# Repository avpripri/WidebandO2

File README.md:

# WidebandO2

An Arduino sketch for controlling a Bosch LSU 4.9 Wideband Lambda sensor with minimal parts

The board used is the ProMicro (ATMEGA32U)
The project uses Visual Studio Code + PlatformIO but can easily be built in Arduino IDE by renaming main.cpp to main.ino.

## Update Jan-2021

Changes:
- PlatformIO
- ProMicro from Teensy 2.0 (just what I have handy)
- Redrafted the circuit for EasyEDA with gerbers, BOM & PnP for JLPCB orders 

## Required Libraries

* RunningAverage - http://playground.arduino.cc/Main/RunningAverage
* PIDLibrary - http://playground.arduino.cc/Code/PIDLibrary

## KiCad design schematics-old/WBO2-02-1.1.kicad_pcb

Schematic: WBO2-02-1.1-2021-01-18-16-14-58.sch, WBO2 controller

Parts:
C1, C13: 10uf
C2, C7, C15: 1uf
C3, C4: 22p
C5, C6: .1
C14: .1uf
D1, D2: LED
D3: 1N4001
F1: 5A
IC1: ATMEGA8-P; DIL28
K1, K2: CONN_3
L1: 10uh / 340mA
P1: CONN_4
P2, P6, P7: CONN_2
Q1: IRL3803
R1: 100
R2, R9: 1.8k
R3: 18k
R4, R7, R8, R18, R19, R20, R21, R22, R23, R29: 10k
R10: 6.8k
R12: 62ohm
R13, R14: 22k
R15, R16: 12k
R17, R30: 100k
R24, R25, R26, R27, R28: 5k
U2: 7805
U4: LM324
X1: 4mhz

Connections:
/bit0: IC1.28 (PC5(ADC5/SCL)), R23.2
/bit1: IC1.27 (PC4(ADC4/SDA)), R22.2
/bit2: IC1.26 (PC3(ADC3)), R21.2
/bit3: IC1.19 (PB5(SCK)), R20.2
/bit4: IC1.18 (PB4(MISO)), R19.2
/bit5: IC1.14 (PB0(ICP)), R18.2
/nernst: IC1.25 (PC2(ADC2)), K2.1, R10.1
/pump: K2.2 (PM), R12.2, R14.2
/pump-adc: IC1.23 (PC0(ADC0)), R17.1, U4.1
/rcal: K2.3, R12.1, R13.2, U4.6 (-), U4.7
/vref: C13.2, K1.3, R1.1, R30.1
unnamed: C1.1, C6.2, D1.1 (A), IC1.7 (VCC), L1.2, P1.4, R3.1, U2.VO
unnamed: R13.1, R15.2, U4.3 (+)
unnamed: R23.1, R28.1, R29.2
unnamed: R22.1, R27.1, R28.2
unnamed: R21.1, R26.1, R27.2
unnamed: R20.1, R25.1, R26.2
unnamed: R19.1, R24.1, R25.2
unnamed: K1.1, Q1.D
unnamed: R14.1, R16.2, U4.2 (-)
unnamed: D2.1 (A), IC1.6 (PD4(XCK/T0))
unnamed: P6.1, U4.8, U4.9 (-)
unnamed: D2.2 (K), R9.2
unnamed: C14.2, R10.2
unnamed: C14.1, IC1.16 (PB2(SS/OC1B))
unnamed: IC1.15 (PB1(OC1A)), R7.2
unnamed: C2.1, IC1.21 (AREF)
unnamed: R3.2, R4.2, U4.12 (+)
unnamed: IC1.3 (PD1(TXD)), P1.3
unnamed: D1.2 (K), R2.2
unnamed: F1.1, P2.2 (PM)
unnamed: IC1.2 (PD0(RXD)), P1.2
unnamed: R1.2, U4.13 (-), U4.14
unnamed: IC1.17 (PB3(MOSI/OC2)), R8.2
unnamed: IC1.11 (PD5(T1)), Q1.G
unnamed: R15.1, R30.2
unnamed: R16.1, R17.2
unnamed: P7.2 (PM), R18.1, R24.2
unnamed: C15.2, R7.1, U4.5 (+)
unnamed: C7.2, R8.1, U4.10 (+)
unnamed: C5.1, IC1.20 (AVCC), L1.1
unnamed: C4.1, IC1.10 (PB7(XTAL2/TOSC2)), X1.2
unnamed: C3.1, IC1.9 (PB6(XTAL1/TOSC1)), X1.1
VDD: D3.3 (K), F1.2, K1.2 (PM), U2.VI, U4.4 (VDD)
VSS: C1.2, C2.2, C3.2, C4.2, C5.2, C6.1, C7.1, C13.1, C15.1, D3.2 (A), IC1.8 (GND), IC1.22 (AGND), P1.1, P2.1, P6.2 (PM), P7.1, Q1.S, R2.1, R4.1, R9.1, R29.1, U2.GND, U4.11 (VSS)

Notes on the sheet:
SERIAL
OUTPUT2
OUTPUT1
PUMP DRIVER
REFRENCE VOLTAGE
PUMP CURRENT MEASUREMENT
HEATER CONTROL
POWER SUPPLY

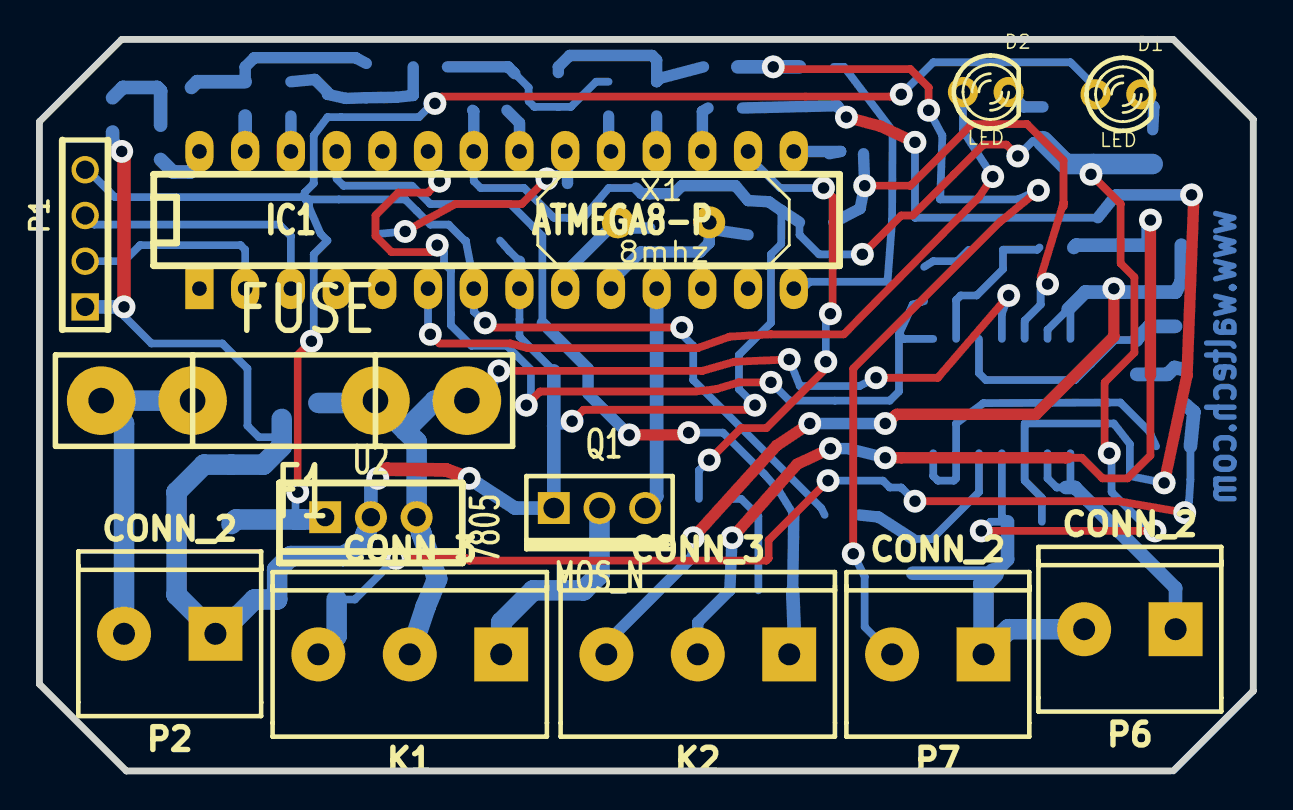
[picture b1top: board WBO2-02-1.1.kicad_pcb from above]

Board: 2 copper layers, 67.4 x 40.6 mm, 53 parts (0 on the bottom side), 45 nets.

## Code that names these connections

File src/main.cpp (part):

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
#define DAC_FACTOR 2550000UL/(LAMBDA_MAX-LAMBDA_MIN)  //don't change: just a calculation pre-compile

//#define MAXPUMP_I 196 // maximum current value for pump (leanest).
#define MAXPUMP_I 329 // maximum current value for pump (leanest).
//see initilize_hardware.h for PWMPUMP_FREQ, if timer OCR1A = PWMPUMP_FREQ, DAC is maxed (5v)
 #define MINPUMP_I 0 // minimum current value for pump.

#define ZERO_CURRENT  116
//#define ZERO_CURRENT  97 //for lower ref v
// 0 current is at 116// now 97 (r4=8.2k ZERO_CURRENT

//#define TARGET_NERNST 832 // lambda=1 value for nurnst, target for pump pid
#define TARGET_NERNST 821 // lambda=1 value for nurnst, target for pump pid
#define TARGET_TEMP 237
#define P_temp    350 //was 450
#define I_temp    100 //5
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uint8_t heat_power; //global value fed to timer0 for heater pwm
uint16_t ADC_data;  //read the ADC into this

volatile uint16_t nurnst = 0; // value read from adc2 for the nernst cell w/o DC
volatile uint16_t pump = 0;   //measured voltage at pump
uint16_t DC_val = 0;          //value read from adc2 for the nernst cell w/DC

//int16_t IpumpVolts=0;//difference from above proportional to current flowing to pump.
uint16_t measured_temperature;  //measured temperature value. also known as Ri
uint32_t zero_to_5_WB;          //value applied to timer2 to make DAC output

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{
//set up all the pins as inputs and outputs
/*
 *  PC5 //outputs for R2R DAC/not used
 *  PC4
 *  PC3
 *  PB5
 *  PB4
 *  PB0
 *
 *  PD4  LED
 *
 * Nernst DC connection: PB2
 * nch mosfet for heater: PD5
 *
 * PB1 = pump power OC1A timer out
 * PB3 = output voltage OC2 timer output
 *   //ADC:
 * nernst V:  adc2
 * pump			adc0
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
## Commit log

2021-01-21 Modernized It
